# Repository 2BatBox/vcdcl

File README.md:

# Voltage-controlled direct current load.

## Operating conditions
Supply Voltage +19.5(+-2)V  
Load voltage (protected input) -200V to +55V  
Load voltage (unprotected input) 0 to +55V  
Load current (both inputs) 10A  
Load power (continuous) 100W  
Input voltage range 0-10V  
Input frequency (at full input voltage range) 0-2kHz  

## Schematics.

## The first prototype.

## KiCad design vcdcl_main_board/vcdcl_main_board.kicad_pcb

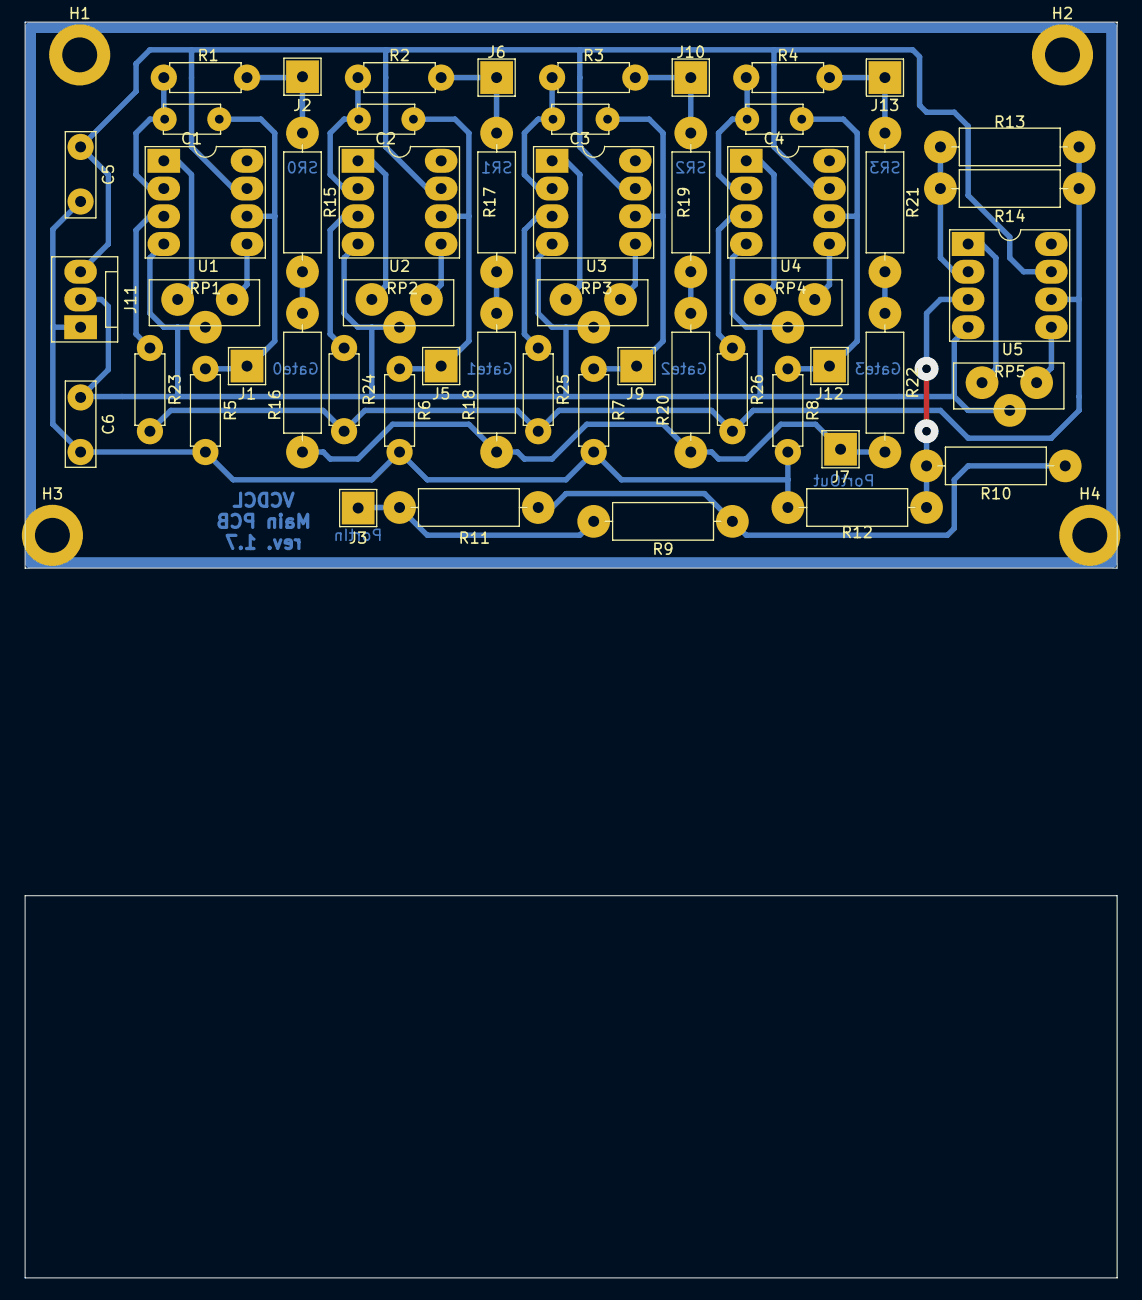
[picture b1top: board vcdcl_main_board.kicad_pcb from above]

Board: 2 copper layers, 100.0 x 115.0 mm, 57 parts (0 on the bottom side), 39 nets.

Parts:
C1, C2, C3, C4: 6.8nF; LUT_C_Disc_D5.0mm_W2.5mm_P5.00mm
C5, C6: 0.22uF; LUT_C_Rect_H7.0mm_W2.0mm_P5.00mm
H1, H2, H3, H4: MountingHole_Pad; MountingHole_3.2mm_M3_DIN965_Pad
J1, J2, J3, J5, J6, J7, J9, J10, J12, J13: Conn_01x01; LUT_PinHeader_1x01_P2.54mm_Vertical
J11: Conn_01x03; LUT_FanPinHeader_1x03_P2.54mm_Vertical
R1, R2, R3, R4, R23, R24, R25, R26: 470; LUT_R_L6.3mm_D2.5mm_P7.62mm_Horizontal
R5, R6, R7, R8: 100k; LUT_R_L6.3mm_D2.5mm_P7.62mm_Horizontal
R9, R11, R15, R17, R19, R21: 16k 0.1%; LUT_R_L9.0mm_D3.2mm_P12.70mm_Horizontal
R10, R12: 1k 0.1%; LUT_R_L9.0mm_D3.2mm_P12.70mm_Horizontal
R13, R14: 1800 0.1%; LUT_R_L9.0mm_D3.2mm_P12.70mm_Horizontal
R16, R18, R20, R22: 24k 0.1%; LUT_R_L9.0mm_D3.2mm_P12.70mm_Horizontal
RP1, RP2, RP3, RP4, RP5: 6.8k; LUT_Potentiometer_SP3_Vertical
U1, U2, U3, U4, U5: LM741; LUT_DIP-8

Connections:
GND: C5.2, C6.1, J11.1, R5.2, R6.2, R7.2, R8.2, R12.2
Gate0: C1.1, J1.1, R5.1, U1.6
Gate1: C2.1, J5.1, R6.1, U2.6
Gate2: C3.1, J9.1, R7.1, U3.6
Gate3: C4.1, J12.1, R8.1, U4.6
unnamed: C1.2, R1.1, U1.2
unnamed: C2.2, R2.1, U2.2
unnamed: C3.2, R3.1, U3.2
unnamed: C4.2, R4.1, U4.2
unnamed: R10.1, R12.1, U5.3
unnamed: R9.1, R10.2, R11.1
unnamed: R13.2, R14.2, U5.2
unnamed: R15.1, R16.2
unnamed: R17.1, R18.2
unnamed: R19.1, R20.2
unnamed: R21.1, R22.2
unnamed: R23.1, U1.3
unnamed: R24.1, U2.3
unnamed: R25.1, U3.3
unnamed: R26.1, U4.3
unnamed: RP1.1, U1.1
unnamed: RP1.3, U1.5
unnamed: RP2.1, U2.1
unnamed: RP2.3, U2.5
unnamed: RP3.1, U3.1
unnamed: RP3.3, U3.5
unnamed: RP4.1, U4.1
unnamed: RP4.3, U4.5
unnamed: RP5.1, U5.1
unnamed: RP5.3, U5.5
PortIn: J3.1, R9.2, R11.2
PortOutC: J7.1, R16.1, R18.1, R20.1, R22.1
SR0: J2.1, R1.2, R15.2
SR1: J6.1, R2.2, R17.2
SR2: J10.1, R3.2, R19.2
SR3: J13.1, R4.2, R21.2
V+: C5.1, J11.3, U1.7, U2.7, U3.7, U4.7, U5.7
V-: C6.2, J11.2, RP1.2, RP2.2, RP3.2, RP4.2, RP5.2, U1.4, U2.4, U3.4, U4.4, U5.4
Vref: R13.1, R14.1, R23.2, R24.2, R25.2, R26.2, U5.6

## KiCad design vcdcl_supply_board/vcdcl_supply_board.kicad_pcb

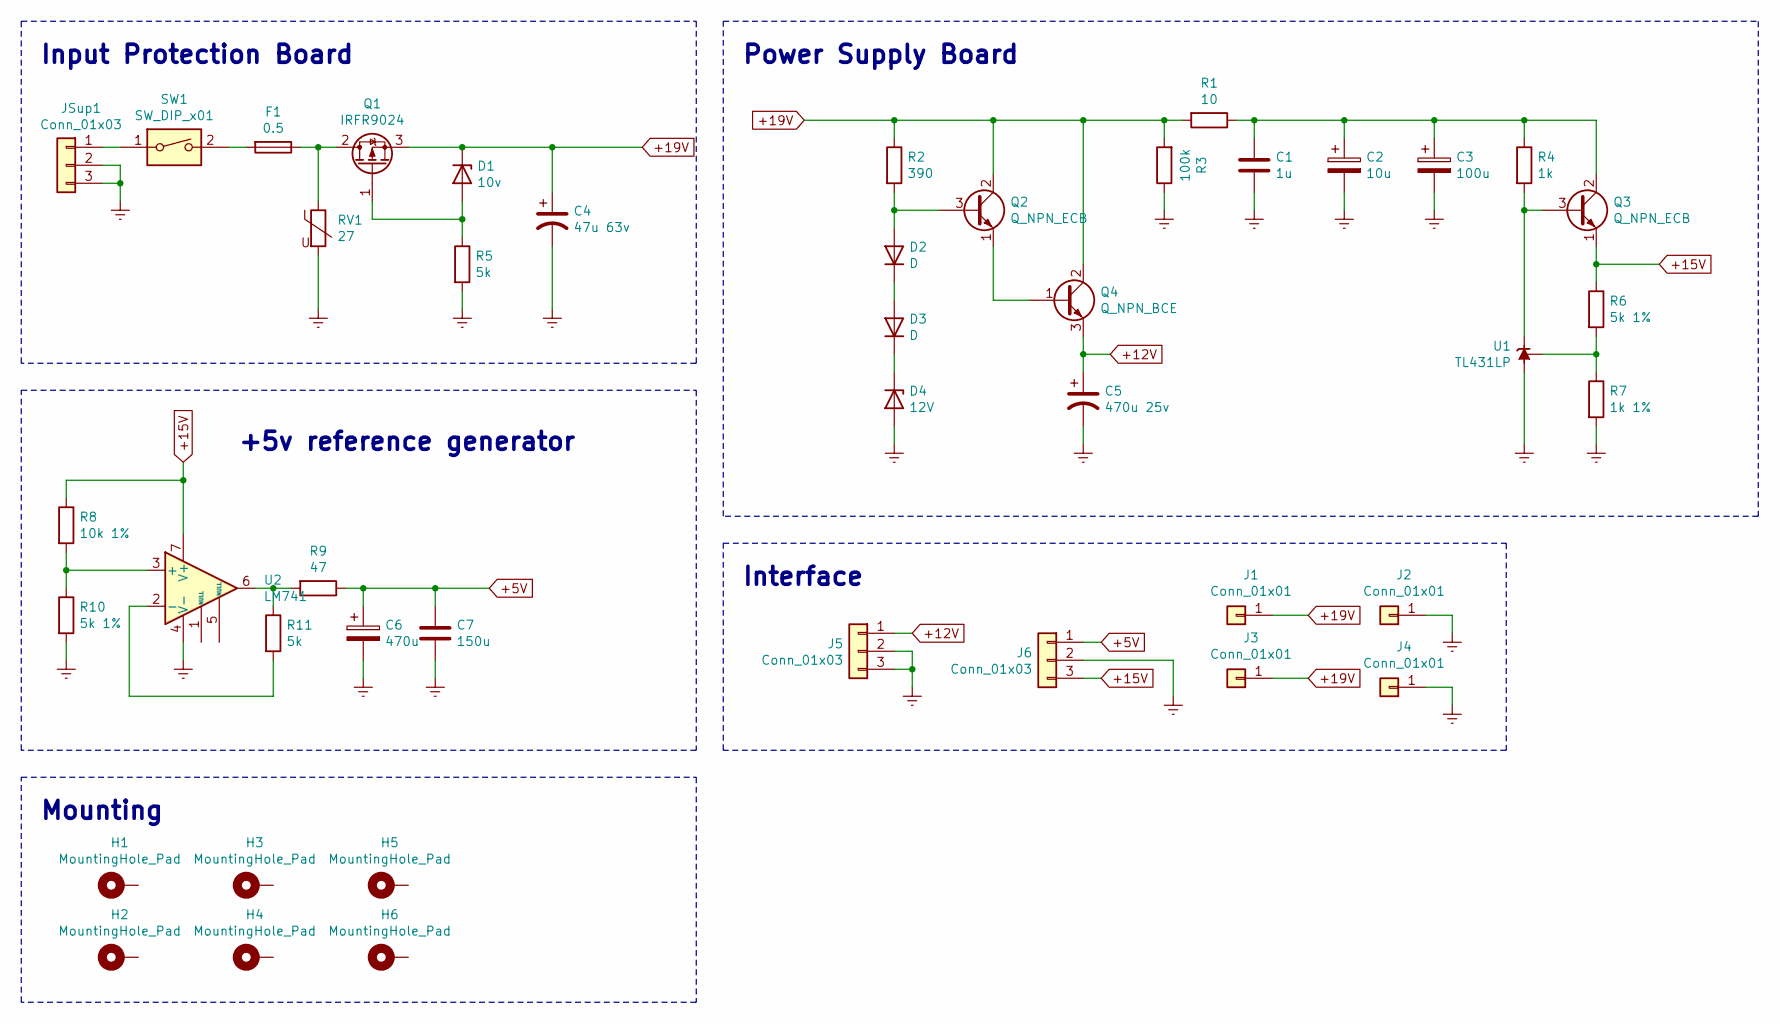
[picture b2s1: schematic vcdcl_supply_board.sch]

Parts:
C1: 1u; LUT_C_Rect_L7.0mm_W4.5mm_P5.00mm
C2: 10u; LUT_CP_Radial_D4.0mm_P2.00mm
C3: 100u; LUT_CP_Radial_D6.3mm_P2.50mm
C4: 47u 63v; LUT_CP_Radial_D8.0mm_P2.50mm
C5: 470u 25v; LUT_CP_Radial_D6.3mm_P2.50mm
C6: 470u; LUT_CP_Radial_D6.3mm_P2.50mm
C7: 150u; LUT_C_Rect_L10.3mm_W5.0mm_P7.50mm
D1: 10v; LUT_D_P10.16mm_Horizontal
D2, D3: D; LUT_D_P7.62mm_Horizontal
D4: 12V; LUT_D_P10.16mm_Horizontal
F1: 0.5; LUT_Fuse-5x20mm_Horizontal_Open
H1, H2, H3, H4, H5, H6: MountingHole_Pad; MountingHole_3.2mm_M3_ISO7380_Pad
J1, J2, J3, J4: Conn_01x01; LUT_PinHeader_1x01_P2.54mm_Vertical
J5, J6: Conn_01x03; LUT_FanPinHeader_1x03_P2.54mm_Vertical
JSup1: Conn_01x03; LUT_BarrelJack_Horizontal
Q1: IRFR9024; LUT_TO-251-3_Vertical
Q2, Q3: Q_NPN_ECB; LUT_TO-92
Q4: Q_NPN_BCE; LUT_TO-220-3_Vertical
R1: 10; LUT_R_L6.3mm_D2.5mm_P7.62mm_Horizontal
R2: 390; LUT_R_L6.3mm_D2.5mm_P7.62mm_Horizontal
R3: 100k; LUT_R_L6.3mm_D2.5mm_P7.62mm_Horizontal
R4: 1k; LUT_R_L6.3mm_D2.5mm_P7.62mm_Horizontal
R5, R11: 5k; LUT_R_L6.3mm_D2.5mm_P7.62mm_Horizontal
R6, R10: 5k 1%; LUT_R_L6.3mm_D2.5mm_P7.62mm_Horizontal
R7: 1k 1%; LUT_R_L6.3mm_D2.5mm_P7.62mm_Horizontal
R8: 10k 1%; LUT_R_L6.3mm_D2.5mm_P7.62mm_Horizontal
R9: 47; LUT_R_L6.3mm_D2.5mm_P7.62mm_Horizontal
RV1: 27; LUT_R_L9.0mm_D3.2mm_P5.08mm_Vertical
SW1: SW_DIP_x01; LUT_PinHeader_1x02_P2.54mm_Vertical
U1: TL431LP; LUT_TO-92
U2: LM741; LUT_DIP-8

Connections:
+5V: C6.1, C7.1, J6.1, R9.1
+12V: C5.1, J5.1, Q4.3 (E)
+15V: J6.3, Q3.1 (E), R6.1, R8.1, U2.7 (V+)
+19V: C4.1, D1.1 (K), J1.1, J3.1, Q1.3 (S), Q2.2 (C), Q4.2 (C), R1.2, R2.1, R3.2
Earth: C1.2, C2.2, C3.2, C4.2, C5.2, C6.2, C7.2, D4.2 (A), J2.1, J4.1, J5.2, J5.3, J6.2, JSup1.2, JSup1.3, R3.1, R5.2, R7.2, R10.2, RV1.2, U1.2 (A), U2.4 (V-)
unnamed: C1.1, C2.1, C3.1, Q3.2 (C), R1.1, R4.1
unnamed: D1.2 (A), Q1.1 (G), R5.1
unnamed: D2.1 (K), D3.2 (A)
unnamed: D2.2 (A), Q2.3 (B), R2.2
unnamed: D3.1 (K), D4.1 (K)
unnamed: F1.1, Q1.2 (D), RV1.1
unnamed: F1.2, SW1.2
unnamed: JSup1.1, SW1.1
unnamed: Q2.1 (E), Q4.1 (B)
unnamed: Q3.3 (B), R4.2, U1.3 (K)
unnamed: R6.2, R7.1, U1.1 (REF)
unnamed: R8.2, R10.1, U2.3 (+)
unnamed: R9.2, R11.1, U2.6
unnamed: R11.2, U2.2 (-)

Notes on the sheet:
Input Protection Board
+5v reference generator
Power Supply Board
Interface
Mounting

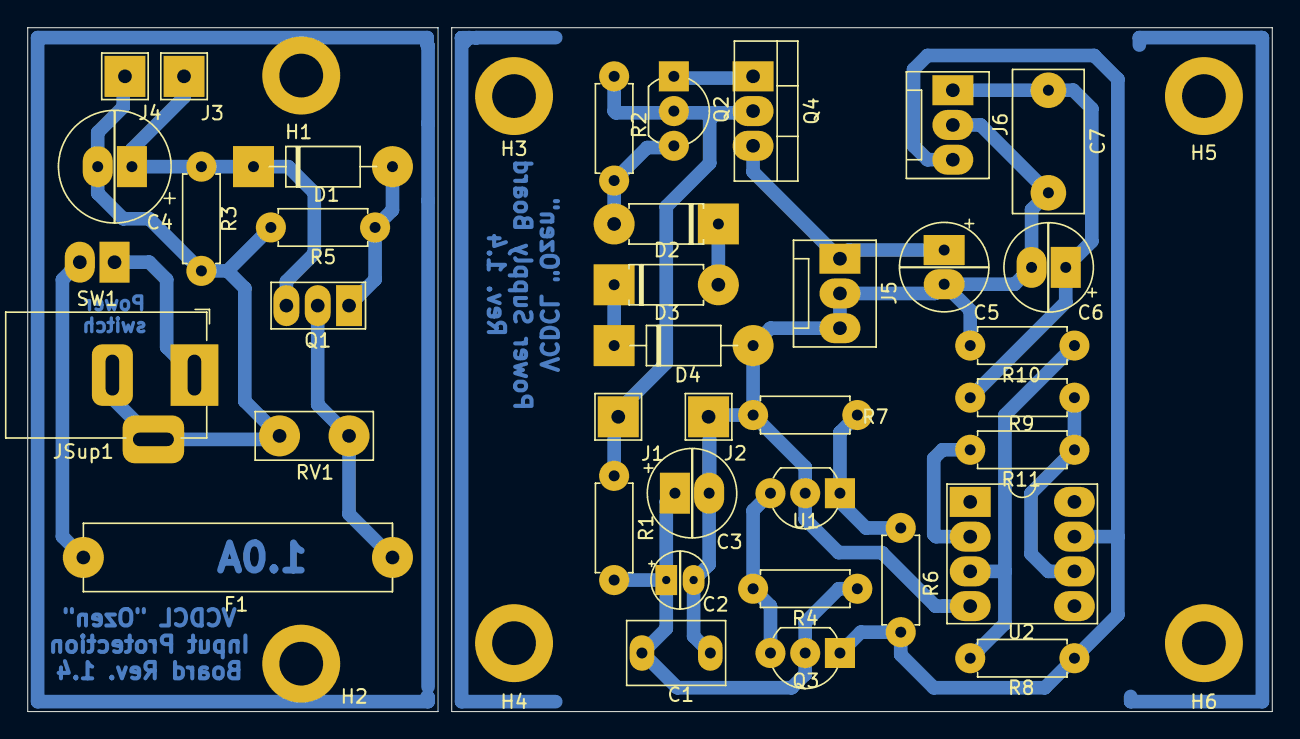
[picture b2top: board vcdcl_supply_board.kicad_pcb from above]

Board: 2 copper layers, 91.0 x 50.0 mm, 44 parts (0 on the bottom side), 19 nets.

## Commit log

2021-12-16 Update supply board
2021-12-16 Append prototype photo
2021-12-24 Remove junk
2022-01-06 Supply board fixes
2022-01-13 Both boards update
2022-04-28 Append schematic pdf files
2022-04-28 Append photos
